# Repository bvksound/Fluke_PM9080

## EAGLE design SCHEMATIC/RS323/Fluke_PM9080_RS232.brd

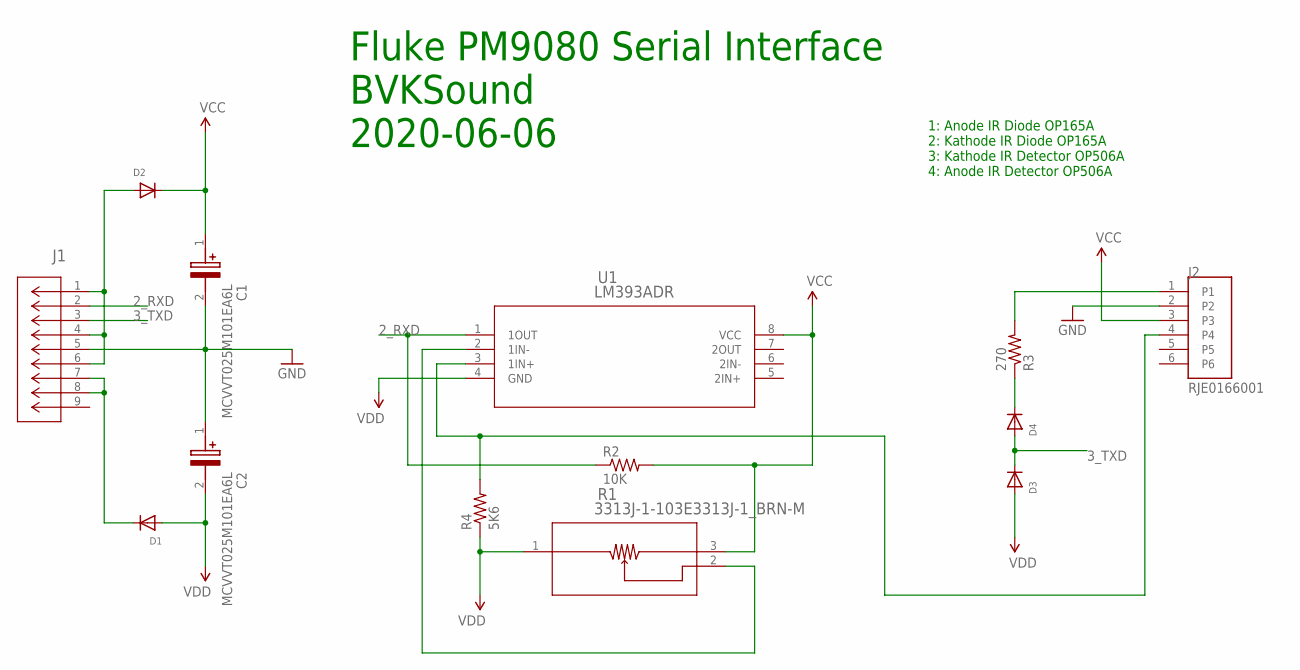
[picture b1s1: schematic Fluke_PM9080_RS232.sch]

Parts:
C1, C2: MCVVT025M101EA6L; CAPAE830X1060N
D1, D2, D3, D4: DIODESOD-123; SOD-123
J1: 5747844-6; CONN_5747844-6_TYC
J2: RJE0166001; AMPHENOL_RJE0166001
R1: 3313J-1-103E3313J-1_BRN-M; 3313J-1_BRN-M
R2: 10K; 1206
R3: 270; 1206
R4: 5K6; 1206
U1: LM393ADR; D8

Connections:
2_RXD: J1.2, R2.1, U1.1 (1OUT)
3_TXD: D3.C, D4.A, J1.3
GND: C1.2 (-), C2.1 (+), J1.5, J2.2
unnamed: D2.A, J1.1, J1.4, J1.6
unnamed: D1.C, J1.7, J1.8
unnamed: R1.2, U1.2 (1IN-)
unnamed: D4.C, R3.1
unnamed: J2.1, R3.2
unnamed: J2.4, R4.2, U1.3 (1IN+)
VCC: C1.1 (+), D2.C, J2.3, R1.3, R2.2, U1.8 (VCC)
VDD: C2.2 (-), D1.A, D3.A, R1.1, R4.1, U1.4 (GND)

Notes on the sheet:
1: Anode IR Diode OP165A 2: Kathode IR Diode OP165A 3: Kathode IR Detector OP506A 4: Anode IR Detector OP506A
Fluke PM9080 Serial Interface BVKSound 2020-06-06

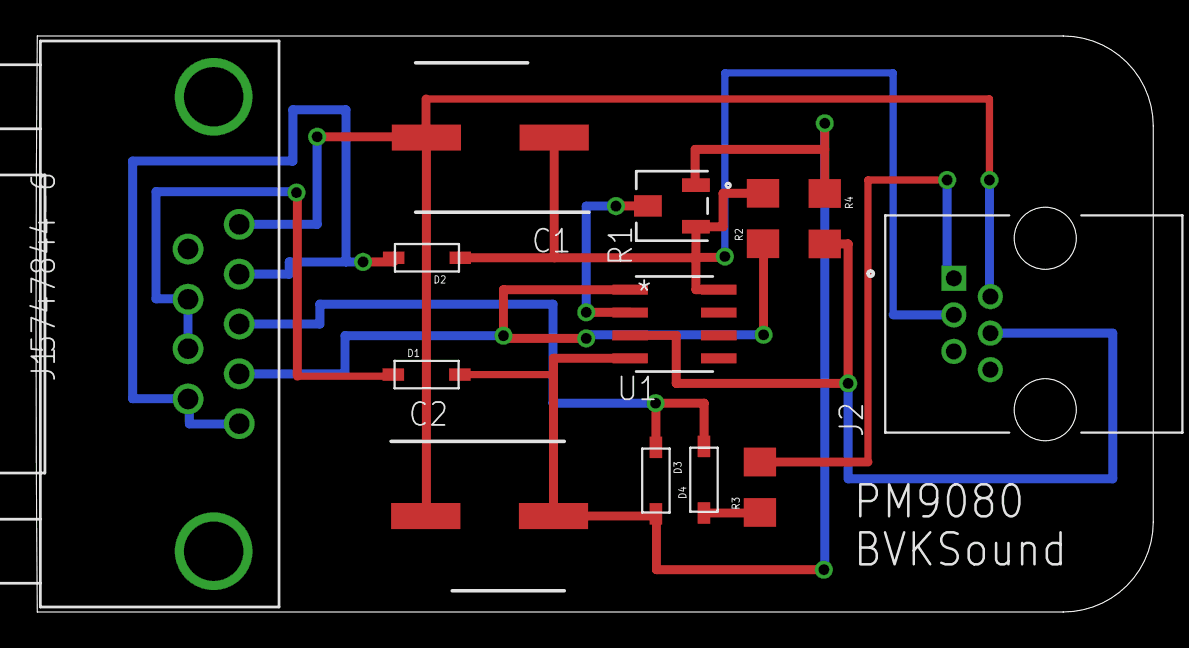
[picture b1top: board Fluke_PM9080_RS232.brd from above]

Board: 2 copper layers, 62.1 x 32.0 mm, 13 parts (0 on the bottom side), 11 nets.

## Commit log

2020-06-05 jumpstart git
2020-06-05 draft
2020-06-06 aded gerber files, pcd design finished

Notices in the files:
parts and their libraries:
SparkFun-Passives: Licensing: Creative Commons ShareAlike 4.0 International - https://creativecommons.org/licenses/by-sa/4.0
COPYRIGHT: Copyright (C) 2018 Accelerated Designs. All rights reserved
